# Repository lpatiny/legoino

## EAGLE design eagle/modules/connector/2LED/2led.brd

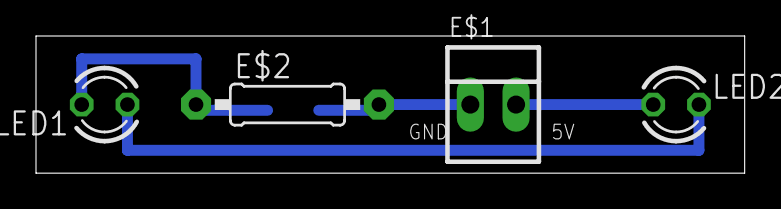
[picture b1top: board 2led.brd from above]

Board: 2 copper layers, 39.4 x 7.6 mm, 5 parts (1 on the bottom side), 4 nets.

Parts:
E$1: 22-23-2021
E$2: 0207/10
LED1, LED2: LED3MM
R1: 1K; R1206

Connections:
S$1: E$1.1, E$2.2, R1.1
S$3: LED1.A, LED2.K
S$4: E$2.1, LED1.K, R1.2
S$5: E$1.2, LED2.A

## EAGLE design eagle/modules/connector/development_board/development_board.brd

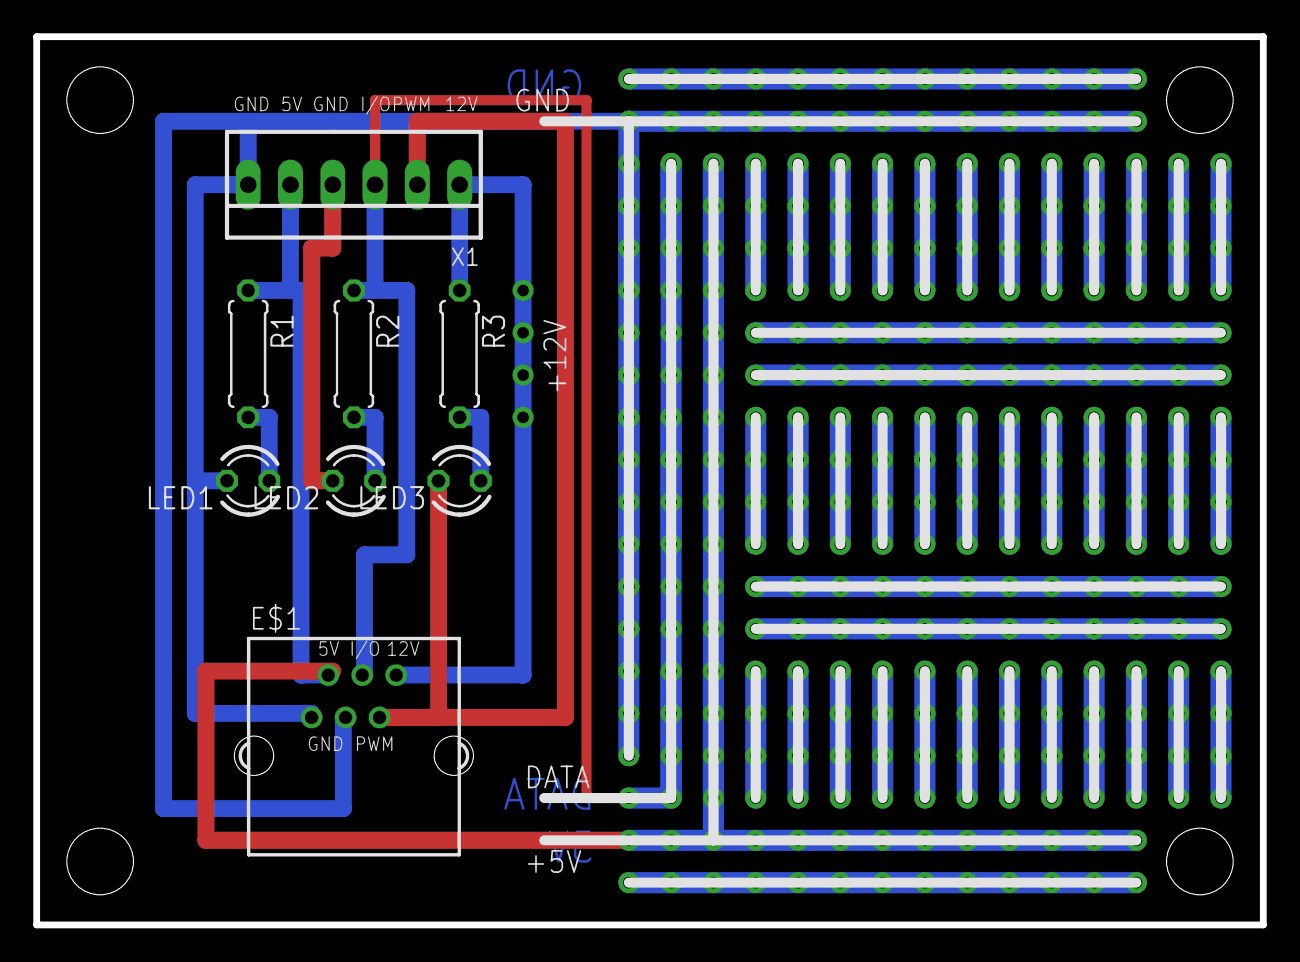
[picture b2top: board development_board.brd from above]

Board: 2 copper layers, 73.7 x 53.3 mm, 8 parts (0 on the bottom side), 9 nets.

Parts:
E$1: YH-55-10
LED1, LED2, LED3: LED3MM
R1, R2, R3: 1k; 0207/7
X1: 22-23-2061

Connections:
S$1: E$1.1, E$1.3, LED1.K, X1.6
S$2: E$1.2, R1.1, X1.5
S$4: E$1.4, R2.1, X1.3
S$5: LED2.K, X1.4
S$6: E$1.5, LED3.K, X1.2
S$7: E$1.6, R3.1, X1.1
S$9: LED1.A, R1.2
S$40: LED2.A, R2.2
S$43: LED3.A, R3.2

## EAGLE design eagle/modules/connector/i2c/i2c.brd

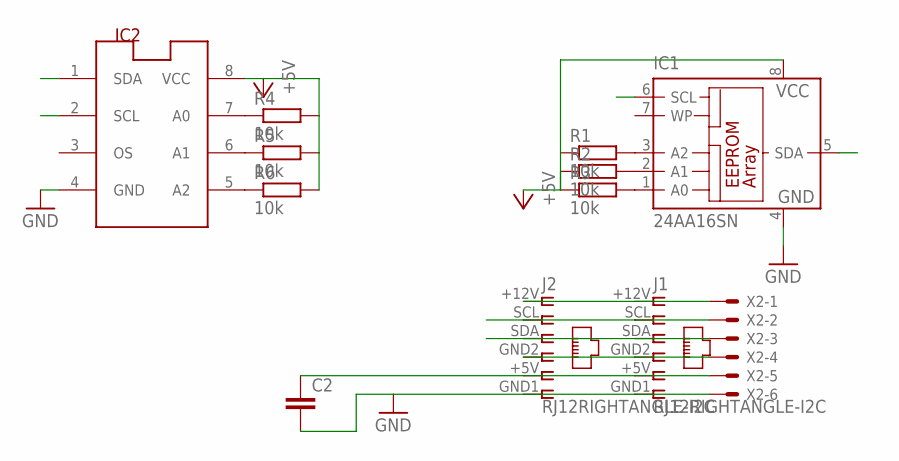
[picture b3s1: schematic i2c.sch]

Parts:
C2: C-EUC1206; C1206
IC1: 24AA16SN; SO-08
IC2: LM75_ICN; SO8_LM75
J1, J2: RJ12RIGHTANGLE-I2C; RJ12-RIGHTANGLE-I2C
R1, R2, R3, R4, R5, R6: 10k; M1206
X2: KK-156-6

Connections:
+5V: IC1.8 (VCC), IC2.8 (VCC), R1.1, R2.1, R3.1, R4.2, R5.2, R6.2
GND: C2.2, IC1.4 (GND), IC2.4 (GND), J1.GND1 (6), J2.GND1 (6), X2.6
unnamed: J1.+12V (1), J2.+12V (1), X2.1
unnamed: IC1.1 (A0), R3.2
unnamed: J1.GND2 (4), J2.GND2 (4), X2.4
unnamed: IC1.2 (A1), R2.2
unnamed: IC1.3 (A2), R1.2
unnamed: IC2.5 (A2), R6.1
unnamed: IC2.7 (A0), R4.1
unnamed: IC2.6 (A1), R5.1
SCL: IC1.6 (SCL), J1.SCL (2), J2.SCL (2), X2.2
SDA: IC1.5 (SDA), J1.SDA (3), J2.SDA (3), X2.3
VCC: C2.1, J1.+5V (5), J2.+5V (5), X2.5

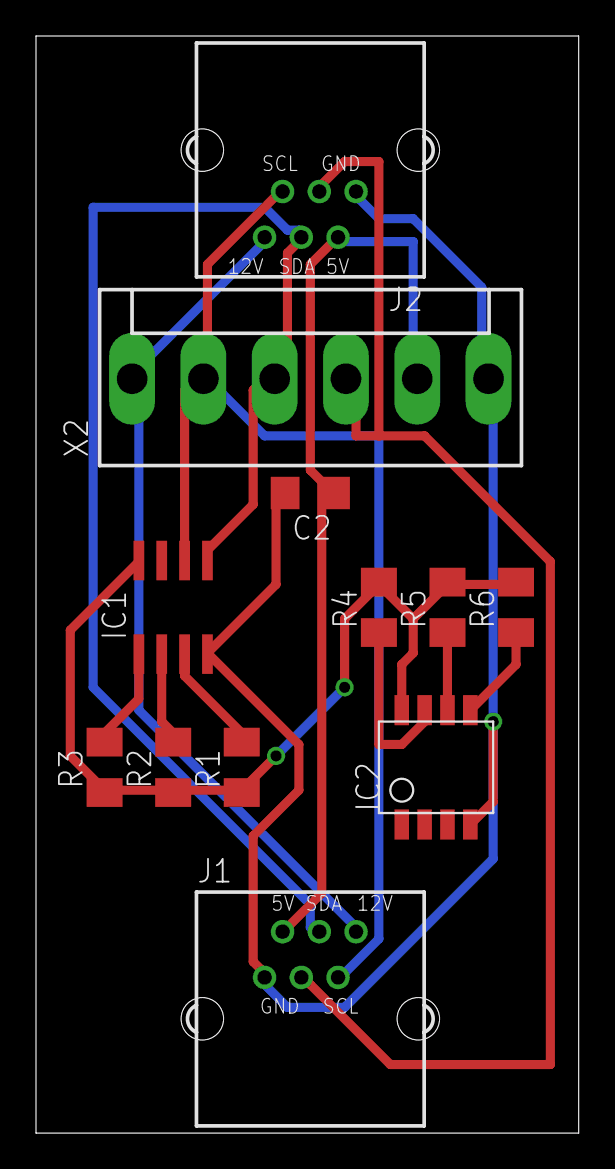
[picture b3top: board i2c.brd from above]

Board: 2 copper layers, 30.1 x 61.0 mm, 12 parts (0 on the bottom side), 13 nets.
